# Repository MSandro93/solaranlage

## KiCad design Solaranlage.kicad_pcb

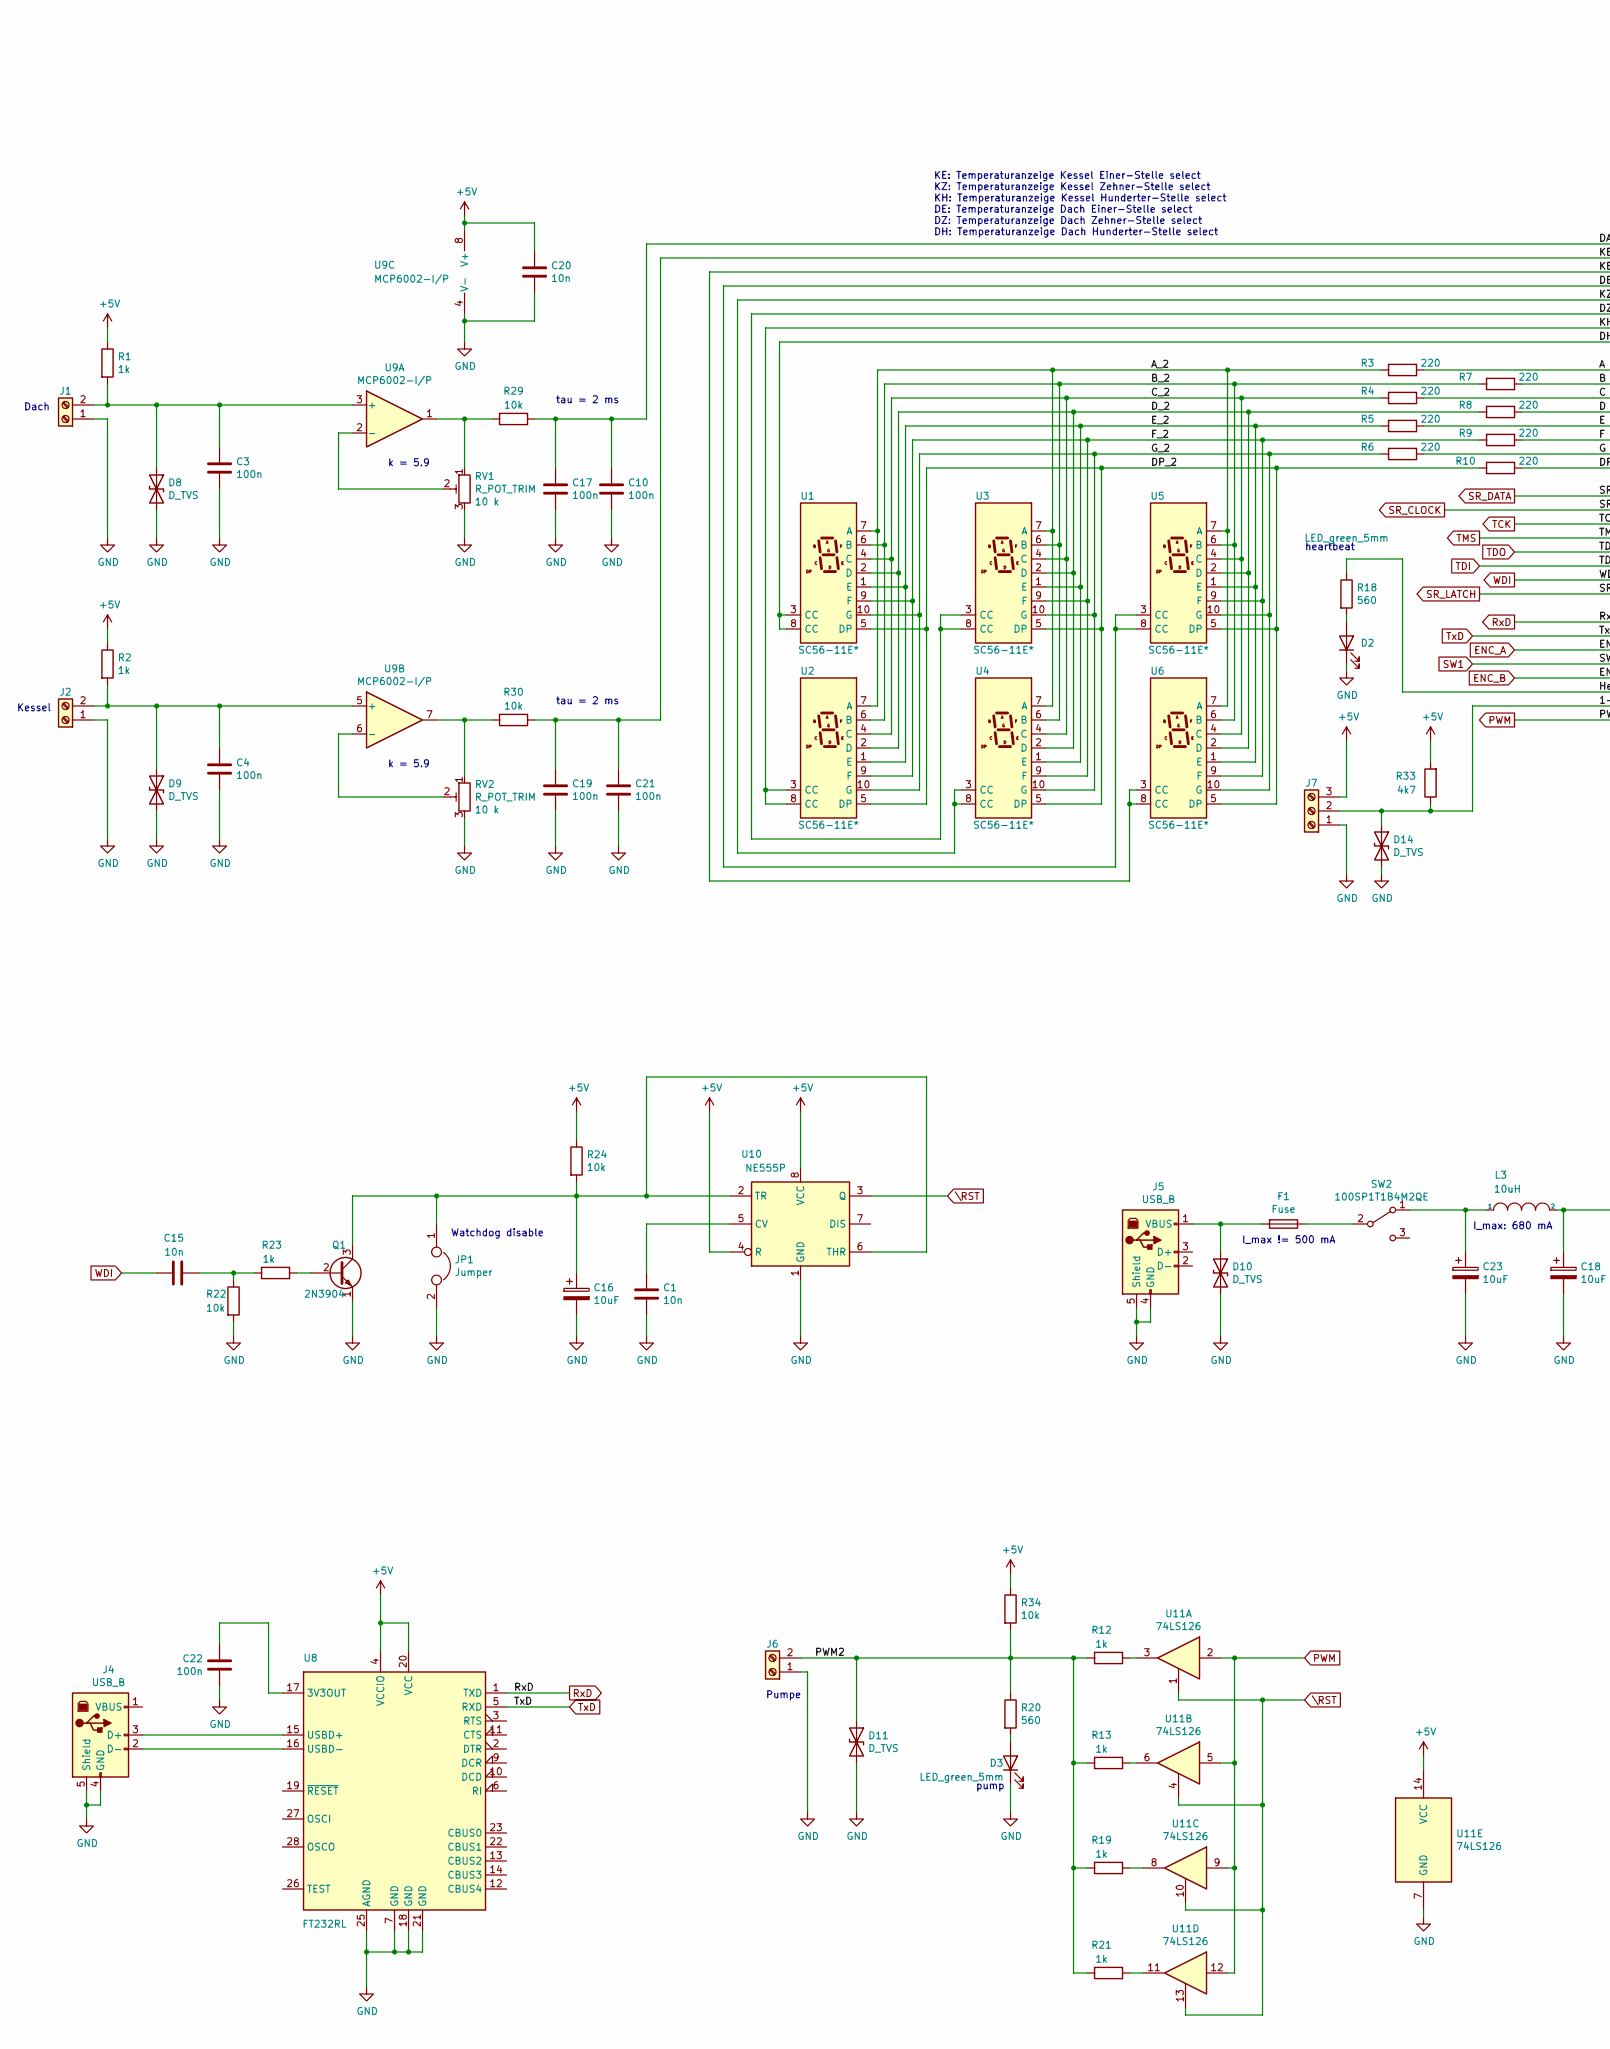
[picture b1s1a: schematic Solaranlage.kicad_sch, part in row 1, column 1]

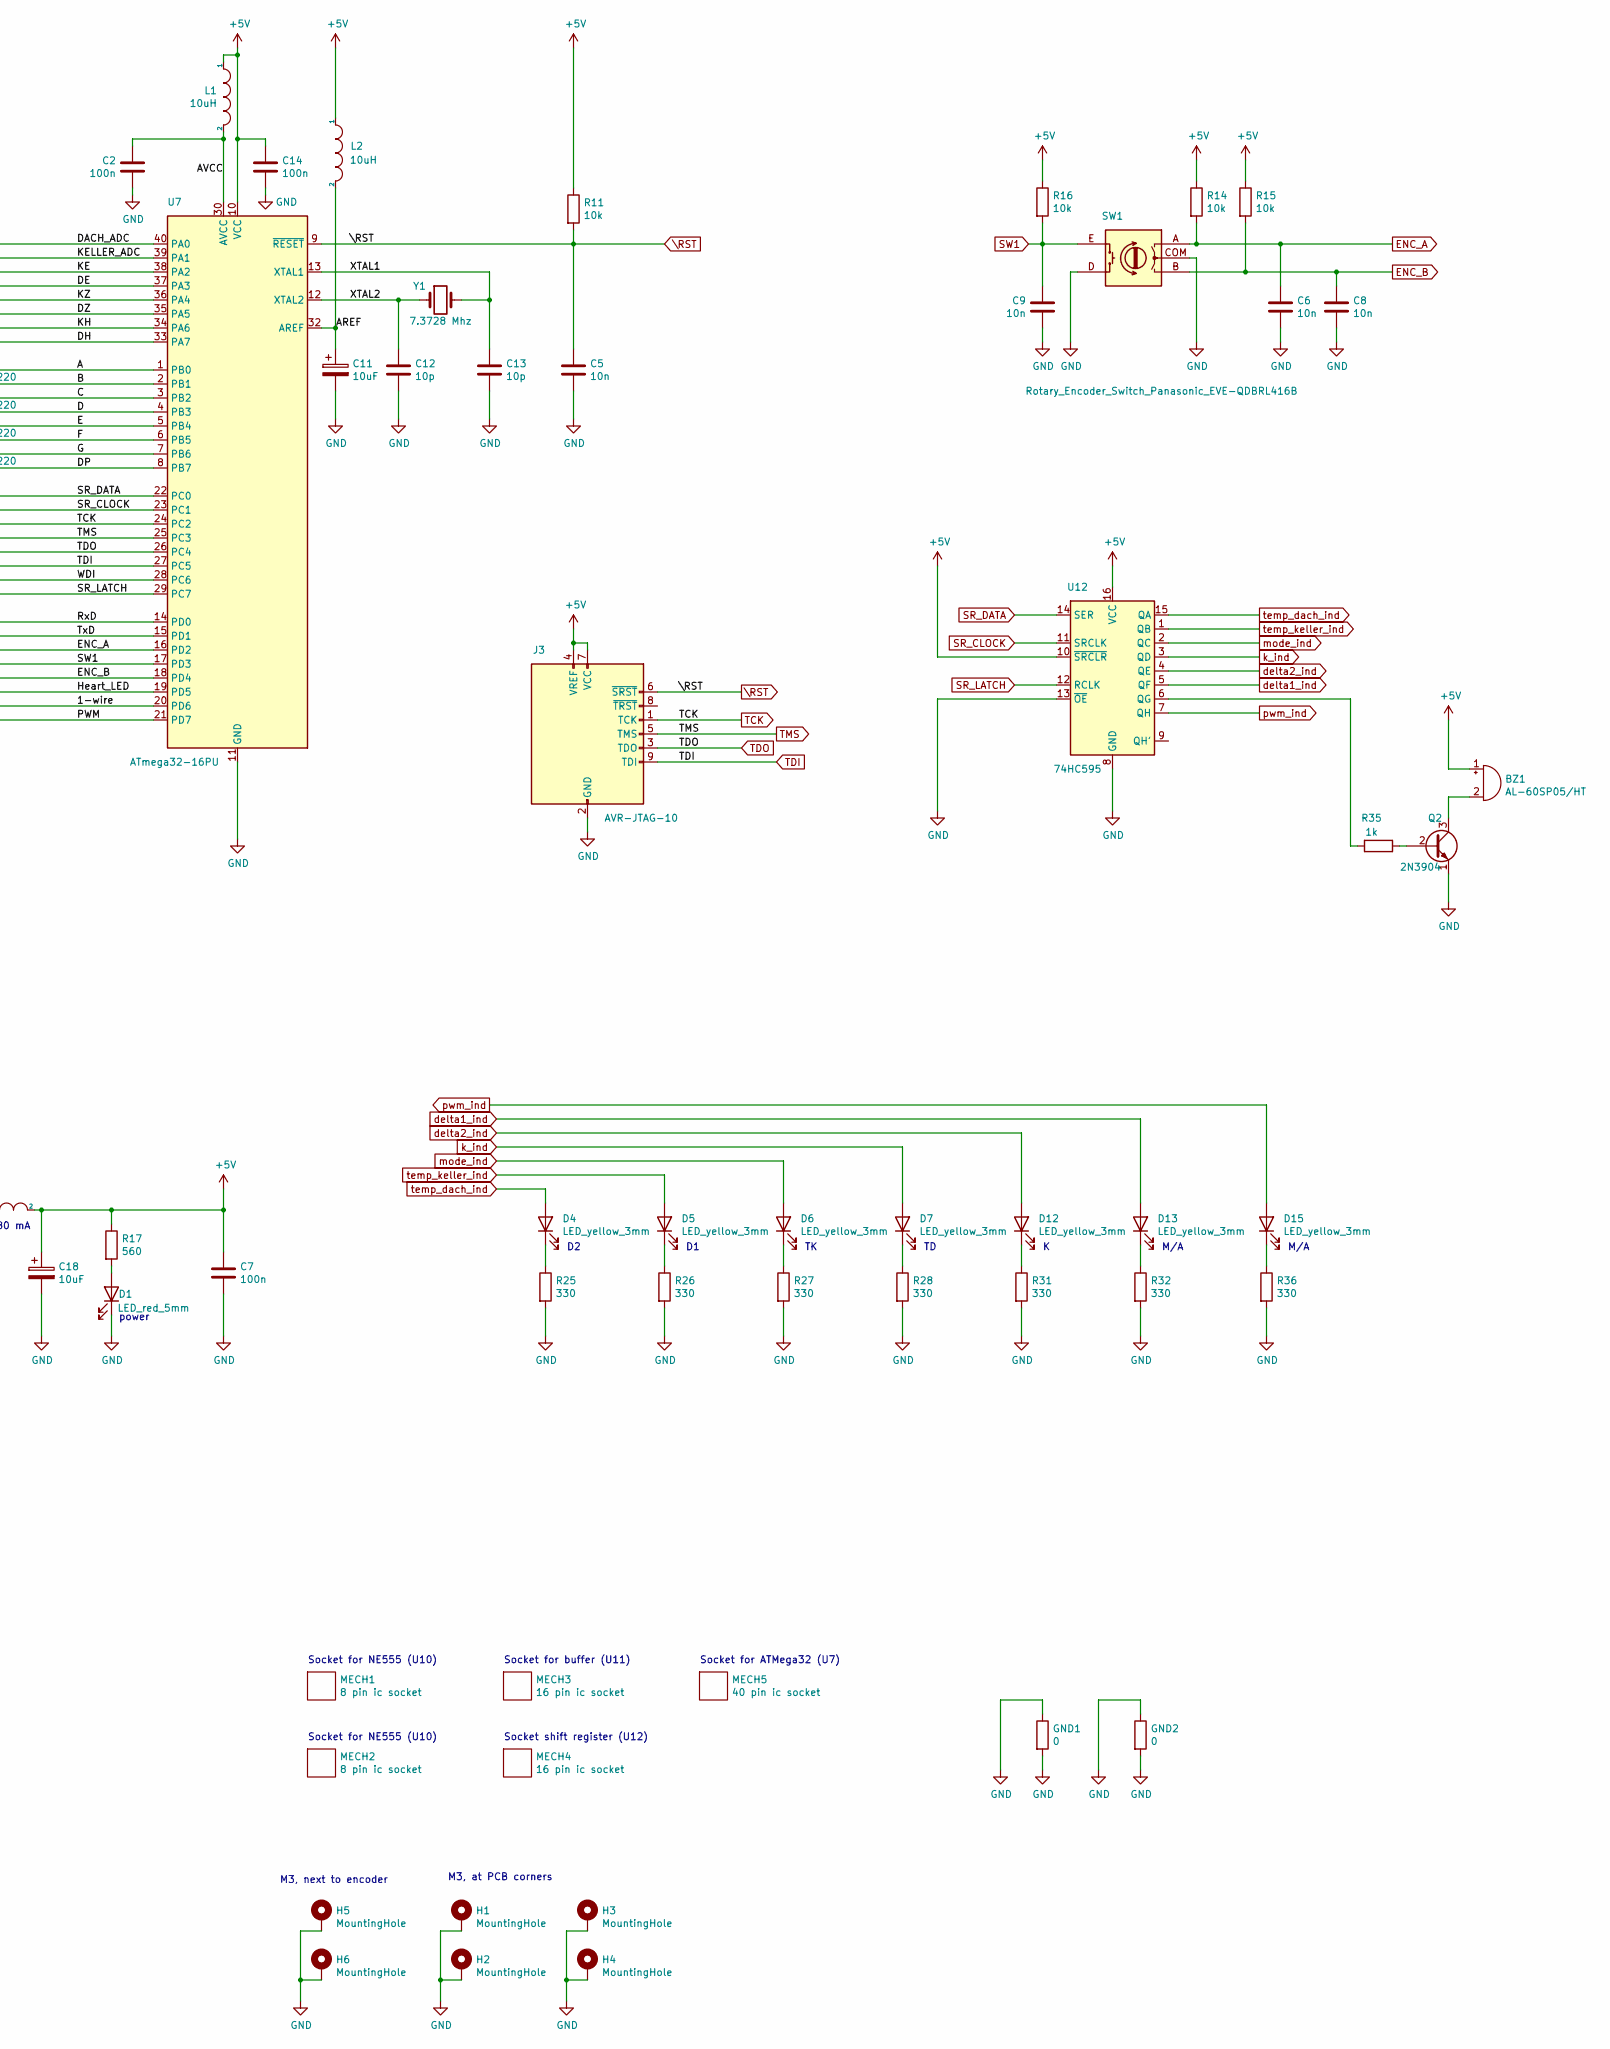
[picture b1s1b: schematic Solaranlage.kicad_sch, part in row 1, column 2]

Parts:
BZ1: AL-60SP05/HT; Buzzer_12x9.5RM7.6
C1, C5, C6, C8, C9, C15, C20: 10n; C_Rect_L7.2mm_W2.5mm_P5.00mm_FKS2_FKP2_MKS2_MKP2
C2, C3, C4, C7, C10, C14, C17, C19, C21, C22: 100n; C_Rect_L7.2mm_W2.5mm_P5.00mm_FKS2_FKP2_MKS2_MKP2
C11, C16, C18, C23: 10uF; CP_Radial_D6.3mm_P2.50mm
C12, C13: 10p; C_Disc_D4.7mm_W2.5mm_P5.00mm
D1: LED_red_5mm; LED_D5.0mm
D2, D3: LED_green_5mm; LED_D5.0mm
D4, D5, D6, D7, D12, D13, D15: LED_yellow_3mm; LED_D3.0mm
D8, D9, D10, D11, D14: D_TVS; D_DO-201_P3.81mm_Vertical_KathodeUp
F1: Fuse; 696101000002
GND1, GND2: 0; R_Axial_DIN0204_L3.6mm_D1.6mm_P7.62mm_Horizontal
H1, H2, H3, H4: MountingHole; MountingHole_3.2mm_M3_Pad_Via
H5, H6: MountingHole; MountingHole_3.2mm_M3_DIN965_Pad
J1, J2, J6: Screw_Terminal_01x02; TerminalBlock_MetzConnect_Type171_RT13702HBWC_1x02_P7.50mm_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
J3: AVR-JTAG-10; PinSocket_2x05_P2.54mm_Horizontal
J4, J5: USB_B; USB_B_Lumberg_2411_02_Horizontal
J7: Screw_Terminal_01x02; TerminalBlock_MetzConnect_Type171_RT13703HBWC_1x03_P7.50mm_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
JP1: Jumper; PinHeader_1x03_P2.54mm_Vertical
L1, L2, L3: 10uH; L_Axial_L9.5mm_D4.0mm_P5.08mm_Vertical_Fastron_SMCC
MECH1, MECH2: 8 pin ic socket; void
MECH3, MECH4: 16 pin ic socket; void
MECH5: 40 pin ic socket; void
Q1, Q2: 2N3904; TO-92L_Wide
R1, R2, R12, R13, R19, R21, R23, R35: 1k; R_Axial_DIN0204_L3.6mm_D1.6mm_P7.62mm_Horizontal
R3, R4, R5, R6, R7, R8, R9, R10: 220; R_Axial_DIN0204_L3.6mm_D1.6mm_P7.62mm_Horizontal
R11, R14, R15, R16, R22, R24, R29, R30, R34: 10k; R_Axial_DIN0204_L3.6mm_D1.6mm_P7.62mm_Horizontal
R17, R18, R20: 560; R_Axial_DIN0204_L3.6mm_D1.6mm_P7.62mm_Horizontal
R25, R26, R27, R28, R31, R32, R36: 330; R_Axial_DIN0204_L3.6mm_D1.6mm_P7.62mm_Horizontal
R33: 4k7; R_Axial_DIN0204_L3.6mm_D1.6mm_P7.62mm_Horizontal
RV1, RV2: R_POT_TRIM; Potentiometer_Bourns_3299W_Vertical
SW1: Rotary_Encoder_Switch_Panasonic_EVE-QDBRL416B; Encoder_Panasonic_EVE-QDBRL416B
SW2: 100SP1T1B4M2QE; sw_pole_3-pol.
U1, U2, U3, U4, U5, U6: SC56-11E*; 7SegmentLED_LTS6760_LTS6780
U7: ATmega32-16PU; DIP-40_W15.24mm
U8: FT232RL; SSOP-28_5.3x10.2mm_P0.65mm
U9: MCP6002-I/P; DIP-8_W7.62mm_LongPads
U10: NE555P; DIP-8_W7.62mm
U11: 74LS126; DIP-14_W7.62mm
U12: 74HC595; DIP-16_W7.62mm
Y1: 7.3728 Mhz; Crystal_HC18-U_Vertical

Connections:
+5V: BZ1.1 (-), C7.1, C14.1, C18.1, C20.1, J3.4 (VREF), J3.7 (VCC), J7.3, L1.1, L2.1, L3.2, R1.1, R2.1, R11.1, R14.1, R15.1, R16.1, R17.1, R24.1, R33.2, R34.1, U7.10 (VCC), U8.4 (VCCIO), U8.20 (VCC), U9.8 (V+), U10.4 (R), U10.8 (VCC), U11.14 (VCC), U12.10 (~SRCLR), U12.16 (VCC)
/1-wire: D14.1 (A1), J7.2, R33.1, U7.20 (PD6)
/A: R3.1, U7.1 (PB0)
/AREF: C11.1, L2.2, U7.32 (AREF)
/AVCC: C2.1, L1.2, U7.30 (AVCC)
/A_2: R3.2, U1.7 (A), U2.7 (A), U3.7 (A), U4.7 (A), U5.7 (A), U6.7 (A)
/B: R7.1, U7.2 (PB1)
/B_2: R7.2, U1.6 (B), U2.6 (B), U3.6 (B), U4.6 (B), U5.6 (B), U6.6 (B)
/C: R4.1, U7.3 (PB2)
/C_2: R4.2, U1.4 (C), U2.4 (C), U3.4 (C), U4.4 (C), U5.4 (C), U6.4 (C)
/D: R8.1, U7.4 (PB3)
/DACH_ADC: C10.1, C17.1, R29.1, U7.40 (PA0)
/DE: U5.3 (CC), U5.8 (CC), U7.37 (PA3)
/DH: U1.3 (CC), U1.8 (CC), U7.33 (PA7)
/DP: R10.1, U7.8 (PB7)
/DP_2: R10.2, U1.5 (DP), U2.5 (DP), U3.5 (DP), U4.5 (DP), U5.5 (DP), U6.5 (DP)
/DZ: U3.3 (CC), U3.8 (CC), U7.35 (PA5)
/D_2: R8.2, U1.2 (D), U2.2 (D), U3.2 (D), U4.2 (D), U5.2 (D), U6.2 (D)
/E: R5.1, U7.5 (PB4)
/E_2: R5.2, U1.1 (E), U2.1 (E), U3.1 (E), U4.1 (E), U5.1 (E), U6.1 (E)
/F: R9.1, U7.6 (PB5)
/F_2: R9.2, U1.9 (F), U2.9 (F), U3.9 (F), U4.9 (F), U5.9 (F), U6.9 (F)
/G: R6.1, U7.7 (PB6)
/G_2: R6.2, U1.10 (G), U2.10 (G), U3.10 (G), U4.10 (G), U5.10 (G), U6.10 (G)
/Heart_LED: R18.1, U7.19 (PD5)
/KE: U6.3 (CC), U6.8 (CC), U7.38 (PA2)
/KELLER_ADC: C19.1, C21.1, R30.1, U7.39 (PA1)
/KH: U2.3 (CC), U2.8 (CC), U7.34 (PA6)
/KZ: U4.3 (CC), U4.8 (CC), U7.36 (PA4)
/PWM2: D11.1 (A1), J6.2, R12.2, R13.2, R19.2, R20.1, R21.2, R34.2
/XTAL1: C13.1, U7.13 (XTAL1), Y1.2
/XTAL2: C12.1, U7.12 (XTAL2), Y1.1
ENC_A: C6.1, R14.2, SW1.A, U7.16 (PD2)
ENC_B: C8.1, R15.2, SW1.B, U7.18 (PD4)
GND: C1.2, C2.2, C3.2, C4.2, C5.2, C6.2, C7.2, C8.2, C9.2, C10.2, C11.2, C12.2, C13.2, C14.2, C16.2, C17.2, C18.2, C19.2, C20.2, C21.2, C22.2, C23.2, D1.1 (K), D2.1 (K), D3.1 (K), D8.2 (A2), D9.2 (A2), D10.2 (A2), D11.2 (A2), D14.2 (A2), GND1.1, GND1.2, GND2.1, GND2.2, H1.1, H2.1, H3.1, H4.1, H5.1, H6.1, J1.1, J2.1, J3.2 (GND), J3.10 (GND), J4.4 (GND), J4.5 (Shield), J5.4 (GND), J5.5 (Shield), J6.1, J7.1, JP1.2, Q1.1 (E), Q2.1 (E), R22.2, R25.2, R26.2, R27.2, R28.2, R31.2, R32.2, R36.2, RV1.3, RV2.3, SW1.COM, SW1.D, U7.11 (GND), U7.31 (GND), U8.7 (GND), U8.18 (GND), U8.21 (GND), U8.25 (AGND), U9.4 (V-), U10.1 (GND), U11.7 (GND), U12.8 (GND), U12.13 (~OE)
unnamed: BZ1.2 (+), Q2.3 (C)
unnamed: C15.2, R22.1, R23.1
unnamed: D1.2 (A), R17.2
unnamed: D2.2 (A), R18.2
unnamed: D3.2 (A), R20.2
unnamed: D4.1 (K), R25.1
unnamed: D5.1 (K), R26.1
unnamed: D6.1 (K), R27.1
unnamed: D7.1 (K), R28.1
unnamed: C3.1, D8.1 (A1), J1.2, R1.2, U9.3 (+)
unnamed: C4.1, D9.1 (A1), J2.2, R2.2, U9.5 (+)
unnamed: D10.1 (A1), F1.2, J5.1 (VBUS)
unnamed: D12.1 (K), R31.1
unnamed: D13.1 (K), R32.1
unnamed: D15.1 (K), R36.1
unnamed: J4.3 (D+), U8.15 (USBD+)
unnamed: J4.2 (D-), U8.16 (USBD-)
unnamed: Q1.2 (B), R23.2
unnamed: C16.1, JP1.1, Q1.3 (C), R24.2, U10.2 (TR), U10.6 (THR)
unnamed: Q2.2 (B), R35.1
unnamed: R12.1, U11.3
unnamed: R13.1, U11.6
unnamed: R19.1, U11.8
unnamed: R21.1, U11.11
unnamed: R29.2, RV1.1, U9.1
unnamed: R30.2, RV2.1, U9.7
unnamed: C23.1, L3.1, SW2.1 (A)
unnamed: F1.1, SW2.2 (B)
unnamed: C22.1, U8.17 (3V3OUT)
unnamed: RV1.2, U9.2 (-)
unnamed: RV2.2, U9.6 (-)
unnamed: C1.1, U10.5 (CV)
unnamed: R35.2, U12.6 (QG)
PWM: U7.21 (PD7), U11.2, U11.5, U11.9, U11.12
RxD: U7.14 (PD0), U8.1 (TXD)
SR_CLOCK: U7.23 (PC1), U12.11 (SRCLK)
SR_DATA: U7.22 (PC0), U12.14 (SER)
SR_LATCH: U7.29 (PC7), U12.12 (RCLK)
SW1: C9.1, R16.2, SW1.E, U7.17 (PD3)
TCK: J3.1 (TCK), U7.24 (PC2)
TDI: J3.9 (TDI), U7.27 (PC5)
TDO: J3.3 (TDO), U7.26 (PC4)
TMS: J3.5 (TMS), U7.25 (PC3)
TxD: U7.15 (PD1), U8.5 (RXD)
WDI: C15.1, U7.28 (PC6)
\RST: C5.1, J3.6 (~SRST), R11.2, U7.9 (~RESET), U10.3 (Q), U11.1, U11.4, U11.10, U11.13
delta1_ind: D13.2 (A), U12.5 (QF)
delta2_ind: D12.2 (A), U12.4 (QE)
k_ind: D7.2 (A), U12.3 (QD)
mode_ind: D6.2 (A), U12.2 (QC)
pwm_ind: D15.2 (A), U12.7 (QH)
temp_dach_ind: D4.2 (A), U12.15 (QA)
temp_keller_ind: D5.2 (A), U12.1 (QB)

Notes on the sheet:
Socket for NE555 (U10)
I_max: 680 mA
Pumpe
k = 5.9
pump
M/A
Kessel
Dach
Watchdog disable
Socket for ATMega32 (U7)
heartbeat
power
tau = 2 ms
I_max != 500 mA
Socket shift register (U12)
M3, next to encoder
M3, at PCB corners
KE: Temperaturanzeige Kessel Einer-Stelle select KZ: Temperaturanzeige Kessel Zehner-Stelle select KH: Temperaturanzeige Kessel Hunderter-Stelle select DE: Temperaturanzeige Dach Einer-Stelle select DZ: Temperaturanzeige Dach Zehner-Stelle select DH: Temperaturanzeige Dach Hunderter-Stelle select
Socket for buffer (U11)

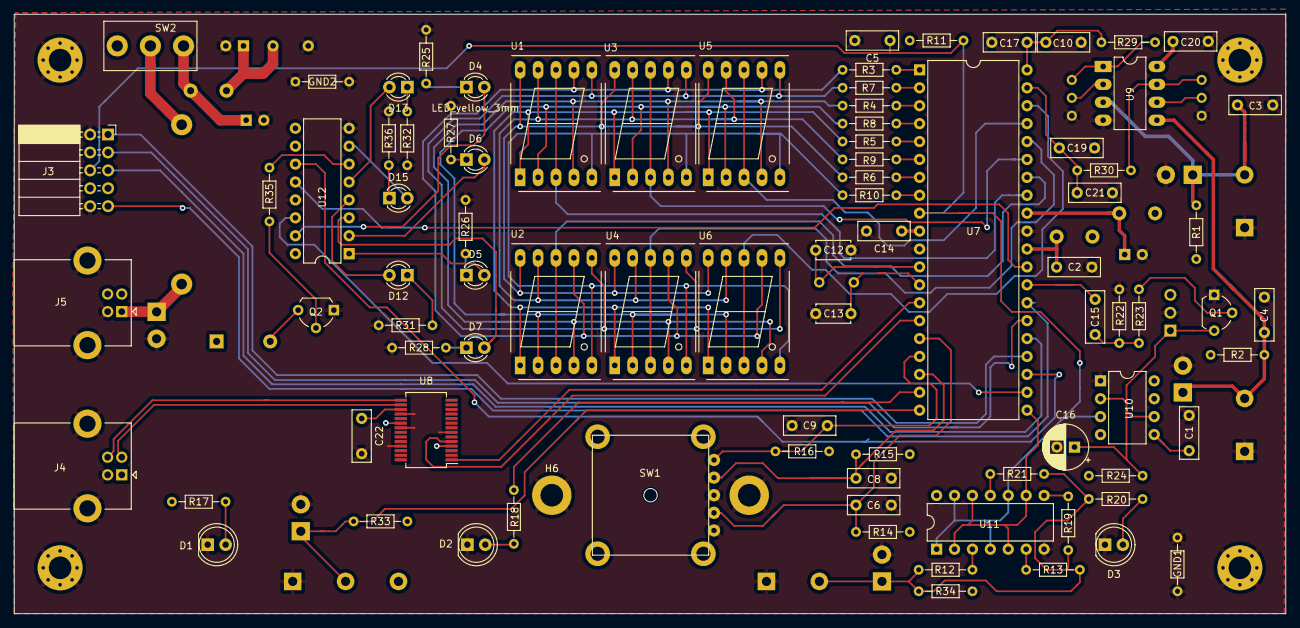
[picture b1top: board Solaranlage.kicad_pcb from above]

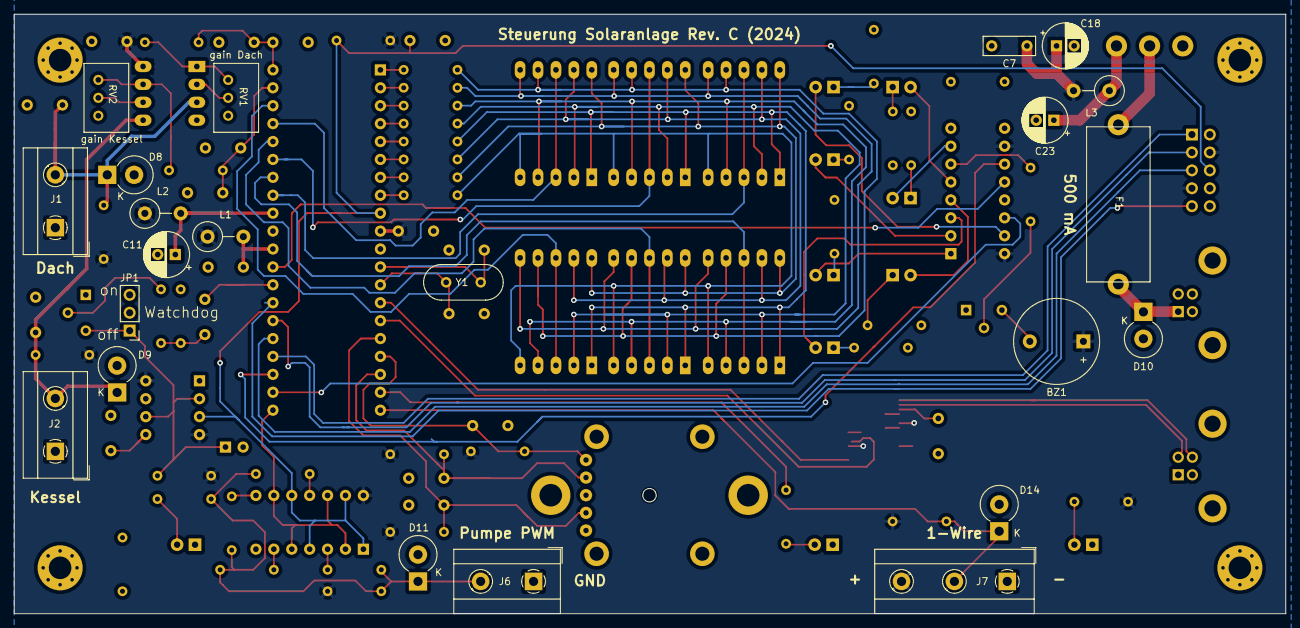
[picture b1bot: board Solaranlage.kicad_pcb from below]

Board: 2 copper layers, 180.3 x 85.0 mm, 119 parts (22 on the bottom side), 88 nets.

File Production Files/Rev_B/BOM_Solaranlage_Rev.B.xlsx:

Quantity | Designator | Value | Supplier | Ordering | Description
1 | BZ1 | AL-60SP05/HT | Conrad | 541347-62 | Buzzer, polarized | o
2 | C12 C13 | 10p | Conrad | 1589402-62 | Unpolarized capacitor
7 | C1 C5 C6 C8 C9 C15 C20 | 10n | Conrad | 1235236-62 | Unpolarized capacitor | o
10 | C2 C3 C4 C10 C14 C17 C19 C21 C7 C22 | 100n | Conrad | 1235240-62 | Unpolarized capacitor | o
4 | C11 C16 C18 C23 | 10uF | Conrad | 1688108-62 | Polarized capacitor | o
5 | D8 D9 D10 D11 D14 | D_TVS | Conrad | 140810-62 | TVS diode | o
2 | D2 D3 | LED_green_5mm | Conrad | 1573746-62 | Light emitting diode | o
1 | D1 | LED_red_5mm | Conrad | 1573740-62 | Light emitting diode | o
6 | D4 D5 D6 D7 D12 D13 | LED_yellow_3mm | Conrad | 1573698-62 | Light emitting diode | o
1 | F1 | Fuse | Conrad | 1898867-62 / 1898865-62 | Fuse | o
1 | J3 | AVR-JTAG-10 | Conrad | 1088159-62 | Atmel 10-pin JTAG connector | o
3 | J1 J2 J6 | Screw_Terminal_01x02 | Digikey | A98092-ND | Screw terminal, single row, 01x02
1 | J7 | Screw_Terminal_01x03 | Digikey | A98093-ND | Screw terminal, single row, 01x03
2 | J4 J5 | USB_B | Conrad | 1883654-62 |  | o
1 | JP1 | Jumper | Conrad | 739443-62 / 734129-62 | Jumper, normally closed | o
3 | L1 L2 L3 | 10uH | Conrad | 440313-62 | Inductor symbol for simulation only | o
1 | MECH5 | Socket for ATMega32 (U7) | Reichelt | GS 40P
2 | MECH1 MECH2 | Socket for NE555 (U10) | Conrad | 189600-62 |  | o
2 | MECH3 MECH4 | Socket for buffer (U11) | Conrad | 189626-62 |  | o
2 | Q1 Q2 | 2N3904 | Reichelt | 2N 3904 | 0.2A Ic, 40V Vce, Small Signal NPN Transistor, TO-92
8 | R3 R4 R5 R6 R7 R8 R9 R10 | 220 | Reichelt | YAG FTE52-220R | Resistor
6 | R25 R26 R27 R28 R31 R32 | 330 | Reichelt | METALL 330 | Resistor
3 | R17 R18 R20 | 560 | Reichelt | YAG FTE52-560R | Resistor
8 | R1 R2 R12 R13 R19 R21 R23 R35 | 1k | Reichelt | VIS C1001FC100 | Resistor
1 | R33 | 4k7 | Reichelt | VIS C4701FC100 | Resistor
9 | R11 R14 R15 R16 R22 R24 R29 R30 R34 | 10k | Reichelt | METALL 10,0K | Resistor
2 | RV1 RV2 | R_POT_TRIM | Conrad | 447564-62 | Trim-potentiometer | o
1 | SW2 | 100SP1T1B4M2QE | Digikey | EG2355-ND | Switch, single pole double throw
1 | SW1 | Rotary_Encoder | Digikey | P12423-ND | Rotary_Encoder
1 | U12 | 74HC595 | Reichelt | 74HC 595 | 8-bit serial in/out Shift Register 3-State Outputs
1 | U11 | 74LS126 | Reichelt | LS 126 | Quad buffer 3-State outputs
1 | U7 | ATmega32-16PU | Reichelt | ATMEGA 32-16 DIP | MCU
1 | U8 | FT232RL | Reichelt | FT 232 RL | USB to Serial Interface, SSOP-28
1 | U9 | MCP6002-I/P | Conrad | 651489-62 | Dual Rail-to-rail CMOS Operational Amplifier, DIP-8/SOIC-8 | o
1 | U10 | NE555P | Reichelt | NE 555 TEX | Precision Timers, 555 compatible, PDIP-8
6 | U1 U2 U3 U4 U5 U6 | SC56-11E* | Reichelt | SC 56-11 RT | One digit 7 segment hyper red LED, common cathode
1 | Y1 | 7.3728 Mhz | Reichelt | 7,3728-HC49U-S | Two pin crystal
1 | - | Nuts M3 | Reichelt | SZK M3X6-200 | 200-pack of M3 screws for mechanical assembly
6 | - | distance bolt M3 | Reichelt | VT DA 12MM | distance bolts for mechanical assembly
1 | - | screw M3 | Reichelt | SK-E M3-100 | 100-pack of M3 nuts for mechanical assembly

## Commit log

2020-08-30 init
2020-10-28 production Rev.A
2020-10-28 fixed designator and value of input-C (C18)
2020-10-29 attached AREF-pin to 5V
2020-10-29 ... and applied to layout
2020-10-29 flipped designator C3 and R1 in silk screen
2020-11-08 fixed reset of ne555
2020-11-09 changed MCU from atmega32 to atmega644 because of availability;added 12p->GND to TCK to make JTAG working
2020-11-09 added Q2 to watchdog circuit;
2020-11-09 changed MCU back to atmega32
2020-11-11 added simualtion for analog amp; applied changes in footprints
2021-01-23 added amps for measureing
2021-01-23 applied changes to layout; added keepouts to supply of MCU and OP; DRC no issues
2021-01-24 resized schematic sheet
2021-01-24 removed simulation files for analog frontend because it was implemented diffrent
2021-01-25 added half done frontplate
2021-01-25 added picture of final state mashine
2021-01-30 removed Q2. Had no plan why it was added. Inserted jumper to disable watchdog during sw-development
2021-02-22 fixed frequency of crystal in schematic
2021-02-22 removed C10 (for common mode blocking of pwm in case of stalling output), because the pwm frequency had to be lowered to 30 Hz
2021-02-23 added 1k serial resistance in the PWM output line to protect GPIO PD7 from burning down
2021-02-25 added LEDs to indicate what the displays show at the moment; added some 3D models; added 10k serial resistors to opamp-outs for TP
2021-02-25 added resistors to layout
2021-02-25 optimization layout
2021-02-27 adapted remarks from schematic review; added output buffer to PWM output
2021-02-28 added some datasheets and ordering numbers
2021-03-01 added shift register for GPIO expansion; edited board shape in order to make the display central; designed frontplate; added MCAD assembly to folder 3D;
2021-03-01 added mcad assembly
2021-03-01 some cleaning
2021-03-02 rounded up corners of cutout for display in the frontplate
2021-03-02 added optional 1-wire 'interface' (J7); added 3D models to terminal blocks
2021-03-02 added input protection and filtering to 1-wire input
2021-03-04 created BOM; added ordering codes; changes some footprints; etc.
2021-03-04 replaced TVS diodes by diodes with higher breakdown voltage to minimize leakage current
2021-03-12 Production state Rev.B
2021-03-12 fixes after receiving RevB PCBs: - increased diameter of H6 to 3.2mm; -decrease radius of hole for encoder to 6.5mm
2021-03-12 added components for mechanical assembly to BOM
2021-03-14 switched pinning of the shift-registers output pins
2021-03-14 increased diameter of the dills for the screws of te finger-grips to 3.2mm
2024-04-16 added PDF of schematic od Rev.B
2024-04-17 Rev.B -> Rev.C
